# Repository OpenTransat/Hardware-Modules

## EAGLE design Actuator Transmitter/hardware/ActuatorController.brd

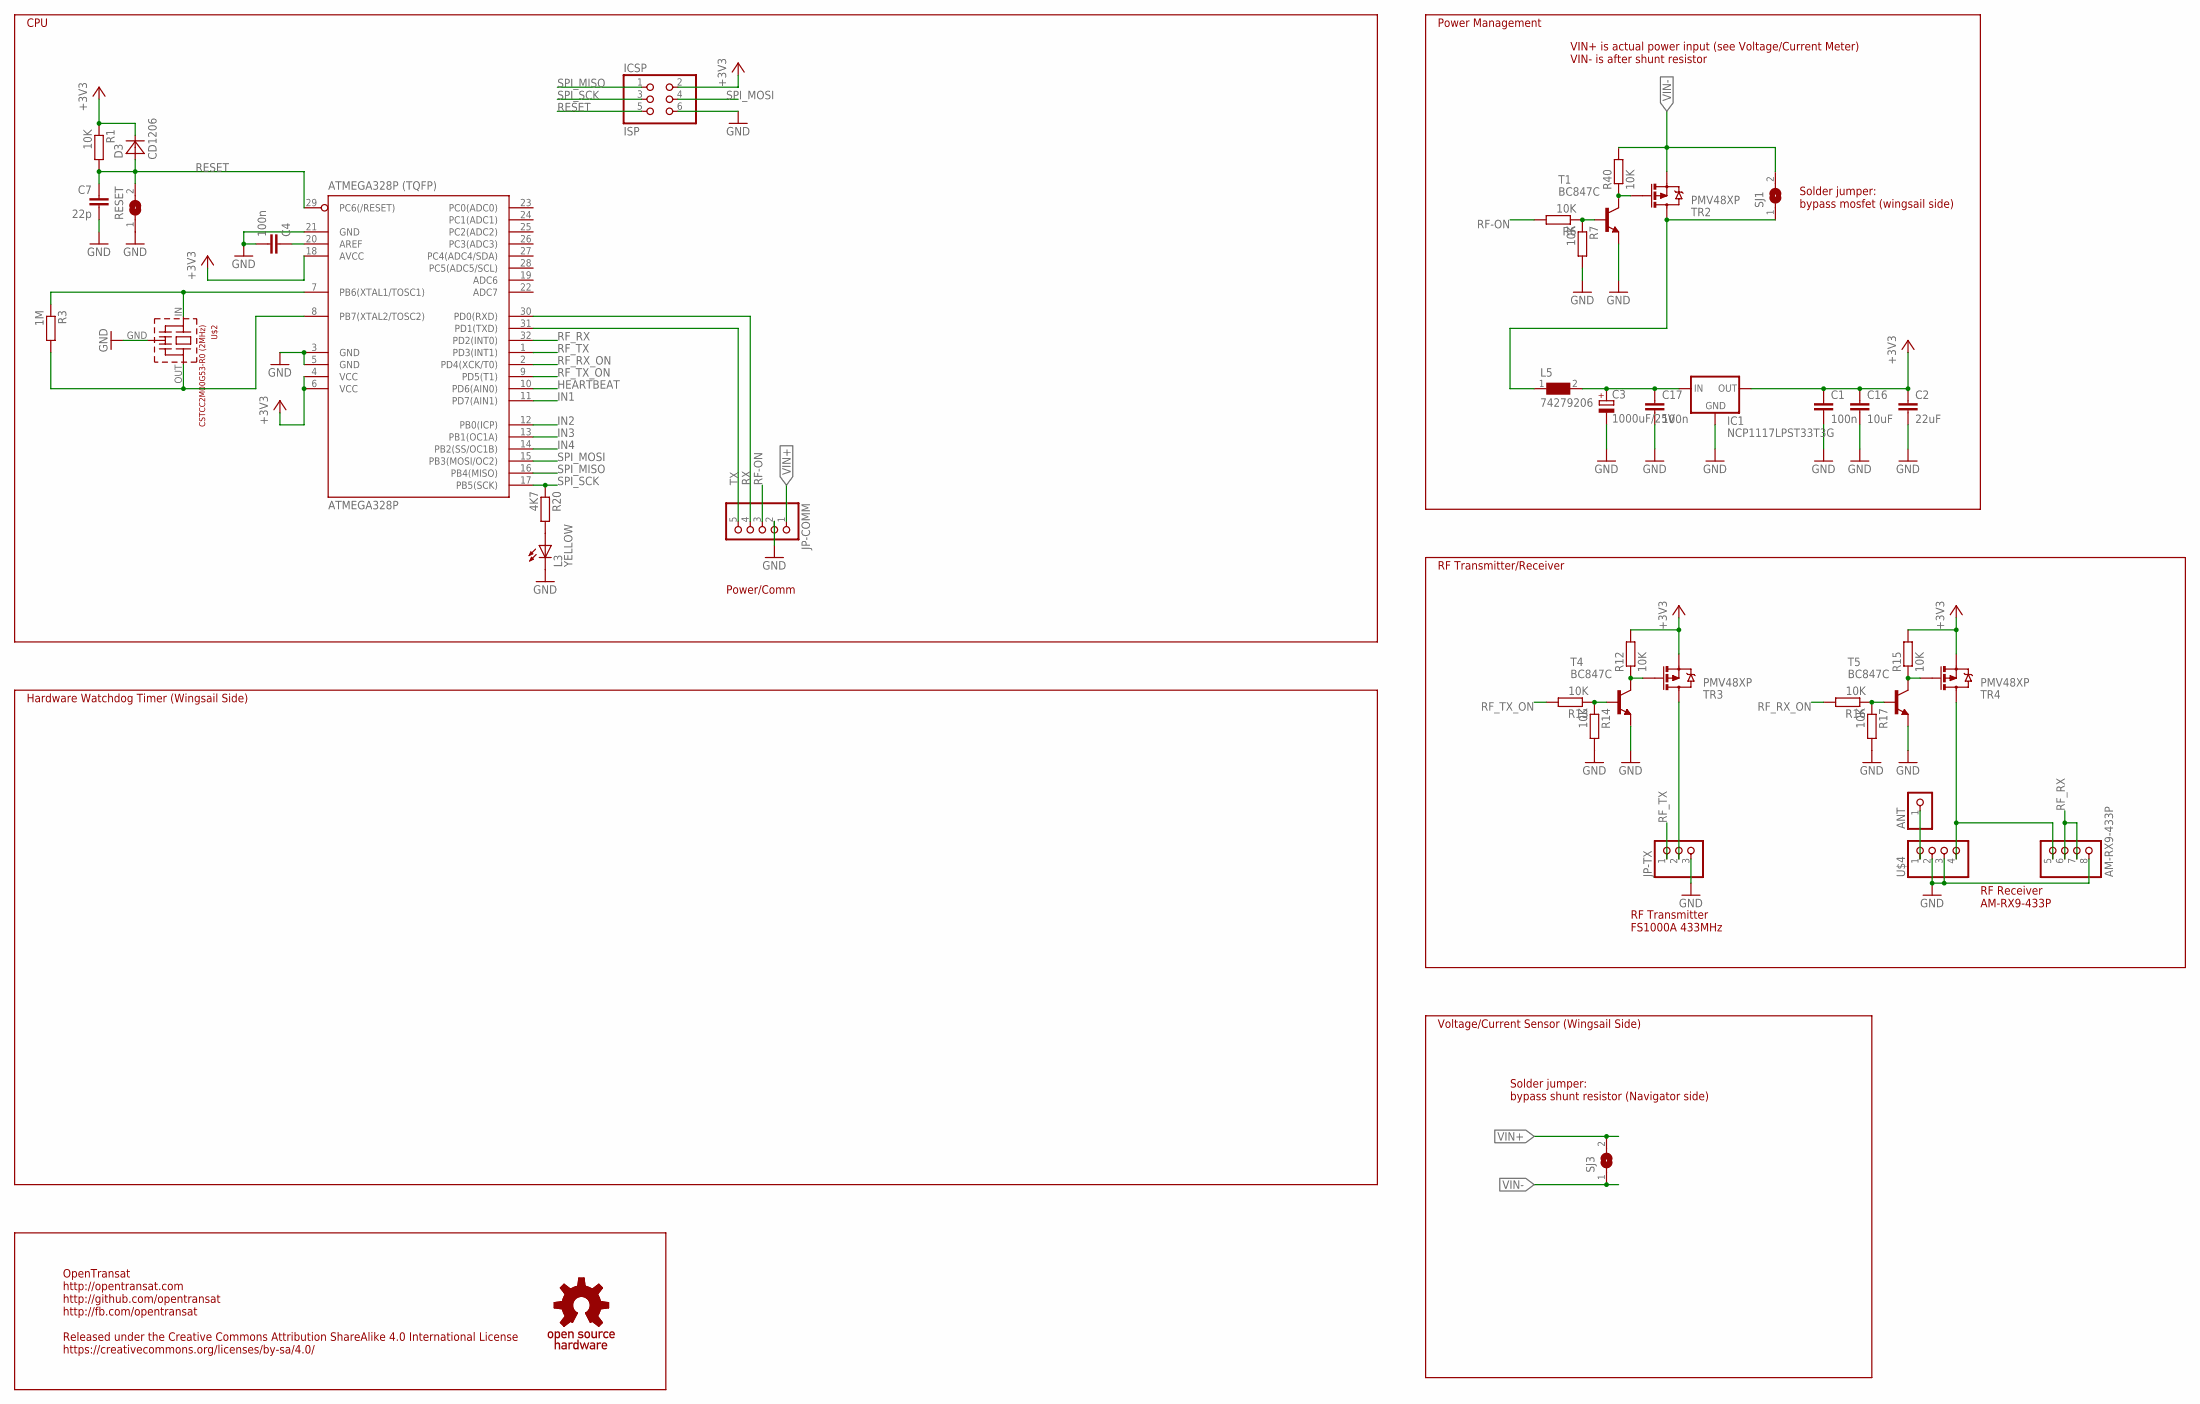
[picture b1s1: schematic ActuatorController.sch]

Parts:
ANT: PINHD-1X1; 1X01
ATMEGA328P: ATMEGA328P (TQFP); TQFP32-08
C1, C4, C17: 100n; C0603
C2: 22uF; C1210
C3: 1000uF/25V; E5-10,5
C7: 22p; C0603
C16: 10uF; C1206
D3: CD1206; R1206
IC1: NCP1117LPST33T3G; SOT223
ICSP: ISP; 2X03
JP-COMM: PINHD-1X5/90; 1X05/90
JP-TX: PINHD-1X3; 1X03
L3: YELLOW; CHIPLED_0805
L5: 74279206; 0805
R1, R6, R7, R12, R13, R14, R15, R16, R17, R40: 10K; R0603
R3: 1M; R0603
R20: 4K7; R0603
RESET: SJW
SJ1, SJ3: SJ
T1, T4, T5: BC847C; SOT23
TR2, TR3, TR4: PMV48XP; SOT23-3
U$1: OSHW_S; OSHWS
U$2: CSTCC2M00G53-R0 (2MHz); CSTCC
U$4: AM-RX9-433P; 1X04

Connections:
+3V3: ATMEGA328P.4 (VCC), ATMEGA328P.6 (VCC), ATMEGA328P.18 (AVCC), C1.1, C2.1, C16.1, D3.2 (C), IC1.2 (OUT), IC1.4 (OUT), ICSP.2, R1.1, R12.2, R15.2, TR3.2 (S), TR4.2 (S)
AREF: ATMEGA328P.20 (AREF), C4.1
GND: ATMEGA328P.3 (GND), ATMEGA328P.5 (GND), ATMEGA328P.21 (GND), C1.2, C2.2, C3.-, C4.2, C7.2, C16.2, C17.2, IC1.1 (GND), ICSP.6, JP-COMM.2, JP-TX.3, L3.C, R7.2, R14.2, R17.2, RESET.1, T1.2 (E), T4.2 (E), T5.2 (E), U$2.GND, U$4.2, U$4.3, U$4.8
HEARTBEAT: ATMEGA328P.10 (PD6(AIN0))
IN1: ATMEGA328P.11 (PD7(AIN1))
IN2: ATMEGA328P.12 (PB0(ICP))
IN3: ATMEGA328P.13 (PB1(OC1A))
IN4: ATMEGA328P.14 (PB2(SS/OC1B))
unnamed: C3.+, C17.1, IC1.3 (IN), L5.2
unnamed: L3.A, R20.2
unnamed: R6.1, R7.1, T1.1 (B)
unnamed: R12.1, T4.3 (C), TR3.1 (G)
unnamed: R13.1, R14.1, T4.1 (B)
unnamed: ANT.1, U$4.1
unnamed: JP-TX.2, TR3.3 (D)
unnamed: R15.1, T5.3 (C), TR4.1 (G)
unnamed: R16.1, R17.1, T5.1 (B)
unnamed: TR4.3 (D), U$4.4, U$4.5
unnamed: R40.1, T1.3 (C), TR2.1 (G)
RESET: ATMEGA328P.29 (PC6(/RESET)), C7.1, D3.1 (A), ICSP.5, R1.2, RESET.2
RF-ON: JP-COMM.3, R6.2
RF_RX: ATMEGA328P.32 (PD2(INT0)), U$4.6, U$4.7
RF_RX_ON: ATMEGA328P.2 (PD4(XCK/T0)), R16.2
RF_TX: ATMEGA328P.1 (PD3(INT1)), JP-TX.1
RF_TX_ON: ATMEGA328P.9 (PD5(T1)), R13.2
RX: ATMEGA328P.30 (PD0(RXD)), JP-COMM.4
SPI_MISO: ATMEGA328P.16 (PB4(MISO)), ICSP.1
SPI_MOSI: ATMEGA328P.15 (PB3(MOSI/OC2)), ICSP.4
SPI_SCK: ATMEGA328P.17 (PB5(SCK)), ICSP.3, R20.1
TX: ATMEGA328P.31 (PD1(TXD)), JP-COMM.5
VBAT-ON: L5.1, SJ1.1, TR2.3 (D)
VIN+: JP-COMM.1, SJ3.2
VIN-: R40.2, SJ1.2, SJ3.1, TR2.2 (S)
XTAL1: ATMEGA328P.8 (PB7(XTAL2/TOSC2)), R3.2, U$2.OUT
XTAL2: ATMEGA328P.7 (PB6(XTAL1/TOSC1)), R3.1, U$2.IN

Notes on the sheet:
OpenTransat http://opentransat.com http://github.com/opentransat http://fb.com/opentransat Released under the Creative Commons Attribution ShareAlike 4.0 International License https://creativecommons.org/licenses/by-sa/4.0/
Power Management
CPU
Voltage/Current Sensor (Wingsail Side)
VIN+ is actual power input (see Voltage/Current Meter) VIN- is after shunt resistor
Power/Comm
RF Receiver AM-RX9-433P
RF Transmitter FS1000A 433MHz
RF Transmitter/Receiver
Hardware Watchdog Timer (Wingsail Side)
Solder jumper: bypass mosfet (wingsail side)
Solder jumper: bypass shunt resistor (Navigator side)

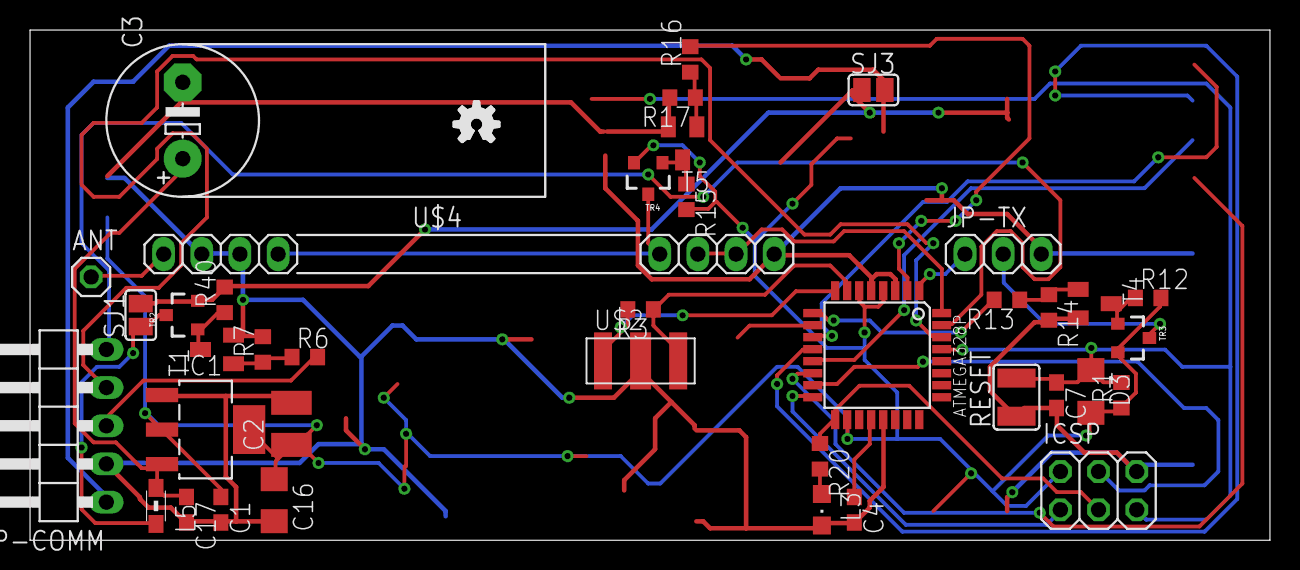
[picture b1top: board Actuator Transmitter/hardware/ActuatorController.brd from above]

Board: 2 copper layers, 82.5 x 34.0 mm, 40 parts (0 on the bottom side), 30 nets.

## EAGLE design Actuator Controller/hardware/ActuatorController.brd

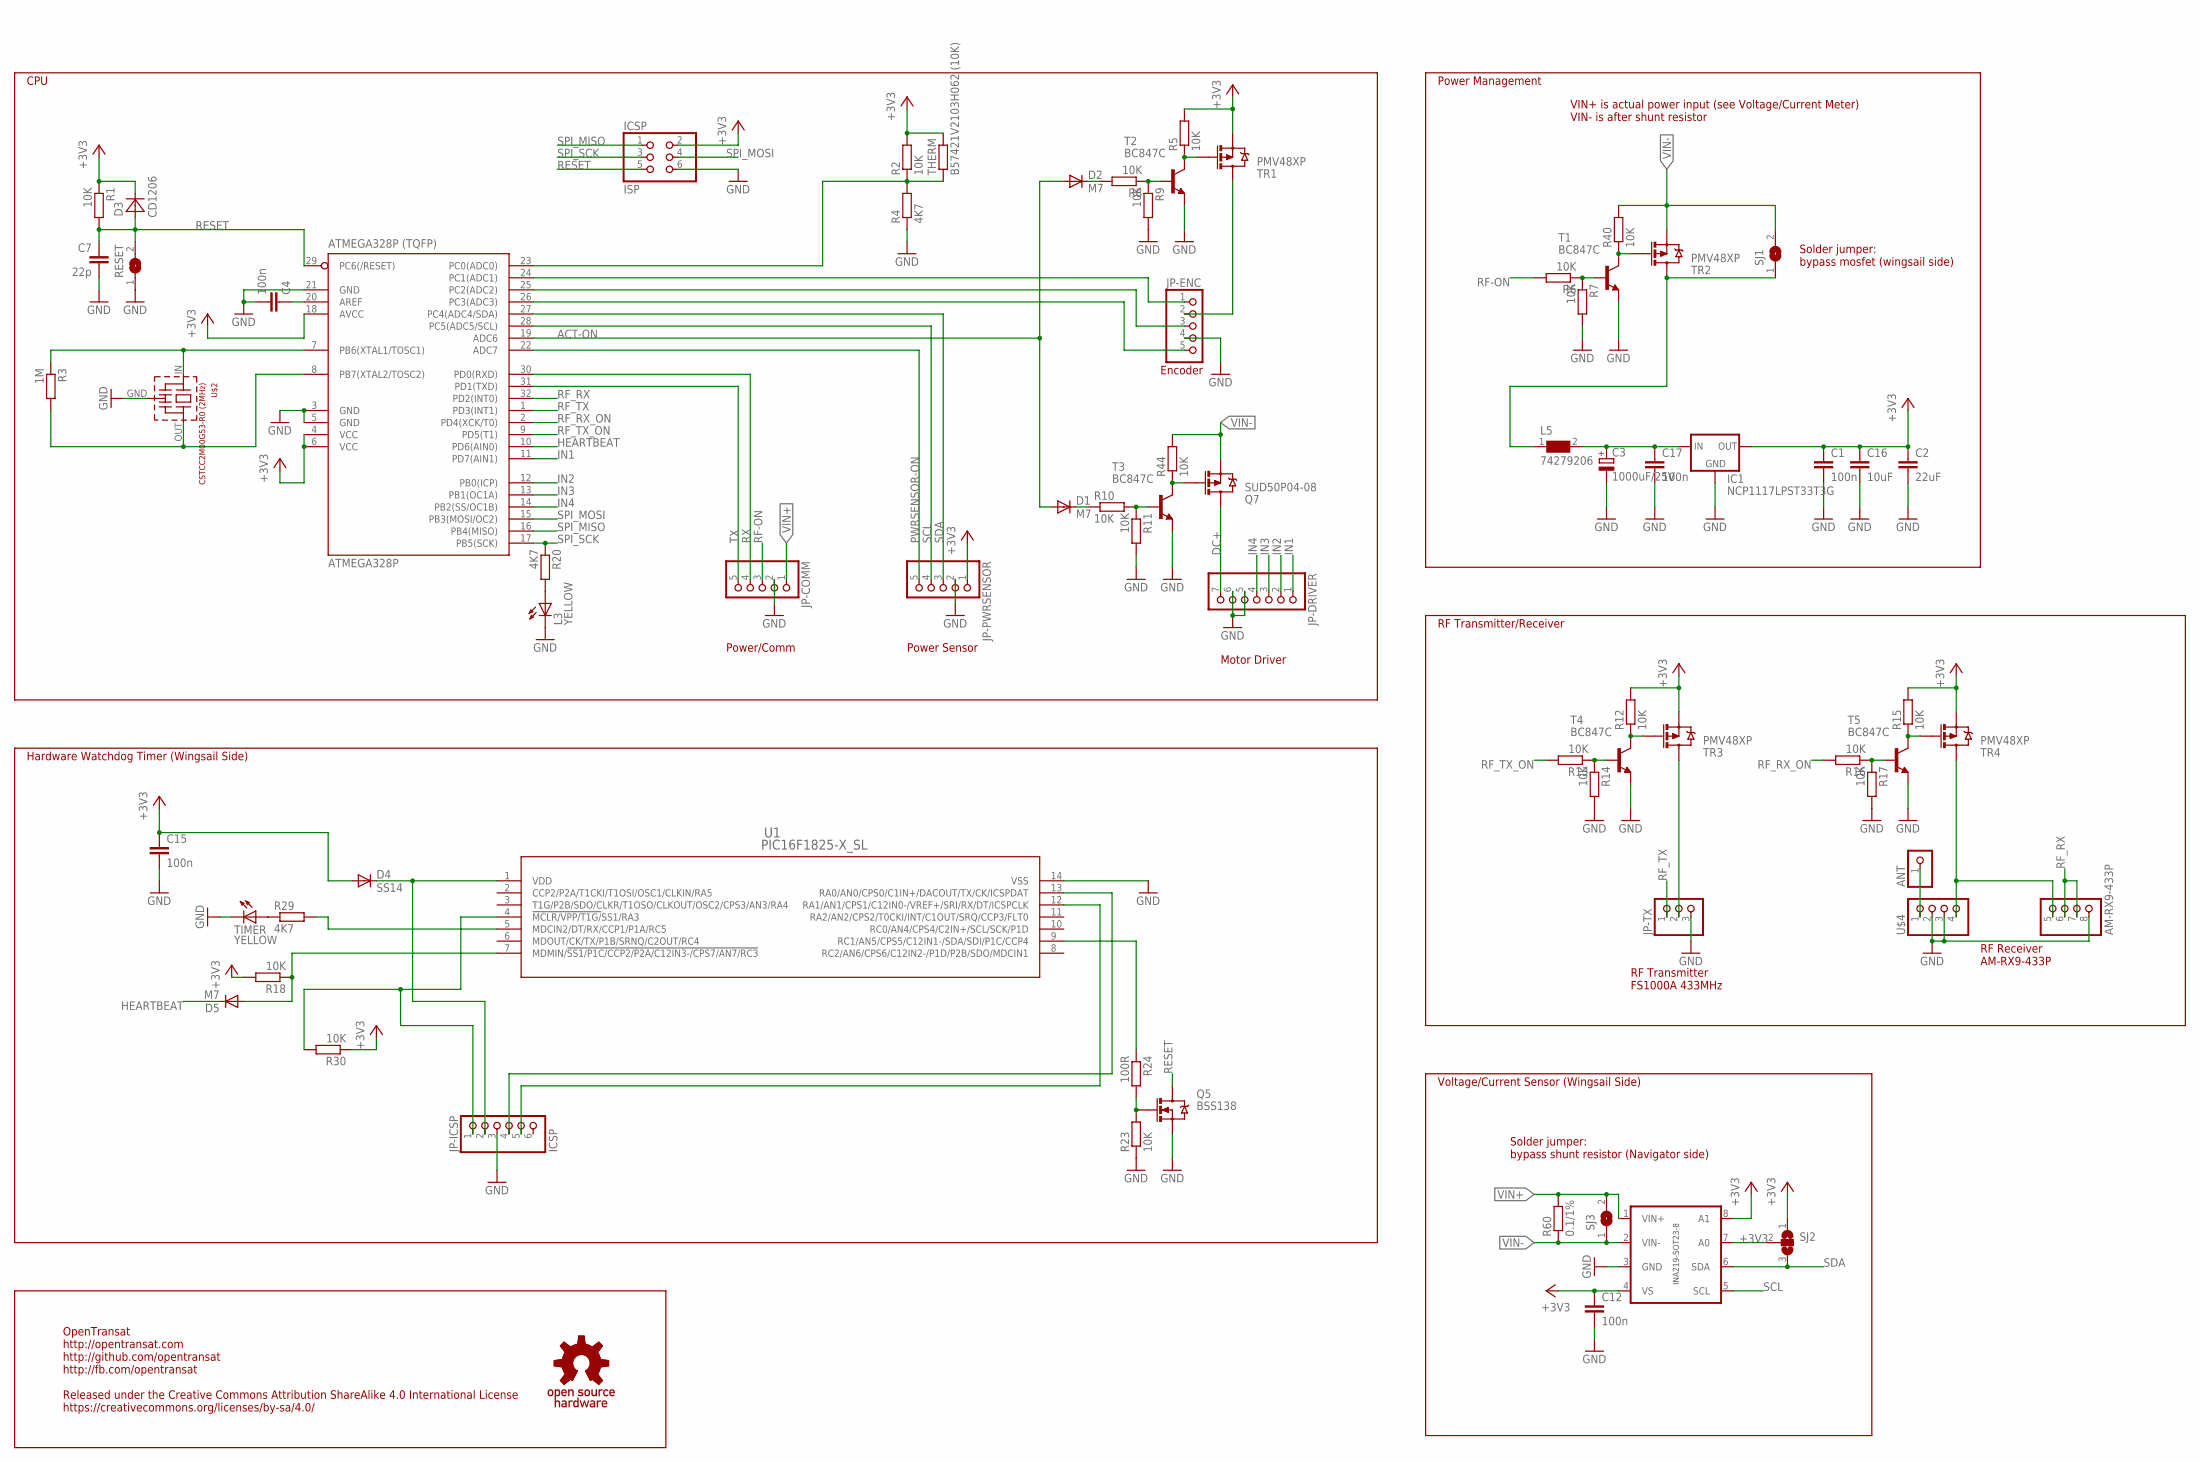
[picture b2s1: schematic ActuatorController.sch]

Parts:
ANT: PINHD-1X1; 1X01
ATMEGA328P: ATMEGA328P (TQFP); TQFP32-08
C1, C4, C12, C15, C17: 100n; C0603
C2: 22uF; C1210
C3: 1000uF/25V; E5-10,5
C7: 22p; C0603
C16: 10uF; C1206
D1, D2, D5: M7; DO-214AC
D3: CD1206; R1206
D4: SS14; DO214AC
IC1: NCP1117LPST33T3G; SOT223
ICSP: ISP; 2X03
JP-COMM: PINHD-1X5/90; 1X05/90
JP-DRIVER: PINHD-1X7/90; 1X07/90
JP-ENC: PINHD-1X5/90; 1X05/90
JP-ICSP: ICSP; 1X06
JP-PWRSENSOR: PINHD-1X5/90; 1X05/90
JP-TX: PINHD-1X3; 1X03
L3: YELLOW; CHIPLED_0805
L5: 74279206; 0805
Q5: BSS138; SOT23-3
Q7: SUD50P04-08; D-PAK_TO252AA
R1, R2, R5, R6, R7, R8, R9, R10, R11, R12, R13, R14, R15, R16, R17, R18, R23, R30, R40, R44: 10K; R0603
R3: 1M; R0603
R4, R20, R29: 4K7; R0603
R24: 100R; R0603
R60: 0.1/1%; R2512
RESET: SJW
SJ1, SJ3: SJ
SJ2: SJ2W; SJ_2
T1, T2, T3, T4, T5: BC847C; SOT23
THERM: B57421V2103H062 (10K); R0603
TIMER: YELLOW; CHIPLED_0805
TR1, TR2, TR3, TR4: PMV48XP; SOT23-3
U1: PIC16F1825-X_SL; SOIC14-N_MC
U$1: OSHW_S; OSHWS
U$2: CSTCC2M00G53-R0 (2MHz); CSTCC
U$3: INA219-SOT23-8; SOT23-8
U$4: AM-RX9-433P; 1X04

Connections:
+3V3: ATMEGA328P.4 (VCC), ATMEGA328P.6 (VCC), ATMEGA328P.18 (AVCC), C1.1, C2.1, C12.1, C15.1, C16.1, D3.2 (C), D4.A, IC1.2 (OUT), IC1.4 (OUT), ICSP.2, JP-PWRSENSOR.1, R1.1, R2.2, R5.2, R12.2, R15.2, R18.2, R30.1, SJ2.1, SJ2.2, THERM.2, TR1.2 (S), TR3.2 (S), TR4.2 (S), U$3.4 (VS), U$3.7 (A0), U$3.8 (A1)
ACT-ON: ATMEGA328P.19 (ADC6), D1.A, D2.A
AREF: ATMEGA328P.20 (AREF), C4.1
DC+: JP-DRIVER.7, Q7.2 (D)
GND: ATMEGA328P.3 (GND), ATMEGA328P.5 (GND), ATMEGA328P.21 (GND), C1.2, C2.2, C3.-, C4.2, C7.2, C12.2, C15.2, C16.2, C17.2, IC1.1 (GND), ICSP.6, JP-COMM.2, JP-DRIVER.5, JP-DRIVER.6, JP-ENC.4, JP-ICSP.3, JP-PWRSENSOR.2, JP-TX.3, L3.C, Q5.2 (S), R4.1, R7.2, R9.2, R11.2, R14.2, R17.2, R23.1, RESET.1, T1.2 (E), T2.2 (E), T3.2 (E), T4.2 (E), T5.2 (E), TIMER.C, U1.14 (VSS), U$2.GND, U$3.3 (GND), U$4.2, U$4.3, U$4.8
HEARTBEAT: ATMEGA328P.10 (PD6(AIN0)), D5.C
IN1: ATMEGA328P.11 (PD7(AIN1)), JP-DRIVER.1
IN2: ATMEGA328P.12 (PB0(ICP)), JP-DRIVER.2
IN3: ATMEGA328P.13 (PB1(OC1A)), JP-DRIVER.3
IN4: ATMEGA328P.14 (PB2(SS/OC1B)), JP-DRIVER.4
unnamed: C3.+, C17.1, IC1.3 (IN), L5.2
unnamed: R5.1, T2.3 (C), TR1.1 (G)
unnamed: L3.A, R20.2
unnamed: R10.2, R11.1, T3.1 (B)
unnamed: ATMEGA328P.23 (PC0(ADC0)), R2.1, R4.2, THERM.1
unnamed: ATMEGA328P.24 (PC1(ADC1)), JP-ENC.1
unnamed: ATMEGA328P.25 (PC2(ADC2)), JP-ENC.3
unnamed: ATMEGA328P.26 (PC3(ADC3)), JP-ENC.5
unnamed: R8.1, R9.1, T2.1 (B)
unnamed: R6.1, R7.1, T1.1 (B)
unnamed: JP-ENC.2, TR1.3 (D)
unnamed: D2.C, R8.2
unnamed: D1.C, R10.1
unnamed: R12.1, T4.3 (C), TR3.1 (G)
unnamed: R13.1, R14.1, T4.1 (B)
unnamed: ANT.1, U$4.1
unnamed: JP-TX.2, TR3.3 (D)
unnamed: R15.1, T5.3 (C), TR4.1 (G)
unnamed: R16.1, R17.1, T5.1 (B)
unnamed: TR4.3 (D), U$4.4, U$4.5
unnamed: D5.A, R18.1, U1.7 (MDMIN/!SS1/P1C/CCP2/P2A/C12IN3-/CPS7/AN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)
unnamed: JP-ICSP.4, U1.13 (RA0/AN0/CPS0/C1IN+/DACOUT/TX/CK/ICSPDAT)
unnamed: Q7.1 (G), R44.1, T3.3 (C)
unnamed: R40.1, T1.3 (C), TR2.1 (G)
unnamed: JP-ICSP.1, R30.2, U1.4 (!MCLR/VPP/T1G/!SS1/RA3)
unnamed: JP-ICSP.5, U1.12 (RA1/AN1/CPS1/C12IN0-/VREF+/SRI/RX/DT/IC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)
unnamed: D4.C, JP-ICSP.2, U1.1 (VDD)
unnamed: R24.1, U1.9 (RC1/AN5/CPS5/C12IN1-/SDA/SDI/P1C/CCP4)
unnamed: Q5.1 (G), R23.2, R24.2
unnamed: R29.2, U1.5 (MDCIN2/DT/RX/CCP1/P1A/RC5)
unnamed: R29.1, TIMER.A
PWRSENSOR-ON: ATMEGA328P.22 (ADC7), JP-PWRSENSOR.5
RESET: ATMEGA328P.29 (PC6(/RESET)), C7.1, D3.1 (A), ICSP.5, Q5.3 (D), R1.2, RESET.2
RF-ON: JP-COMM.3, R6.2
RF_RX: ATMEGA328P.32 (PD2(INT0)), U$4.6, U$4.7
RF_RX_ON: ATMEGA328P.2 (PD4(XCK/T0)), R16.2
RF_TX: ATMEGA328P.1 (PD3(INT1)), JP-TX.1
RF_TX_ON: ATMEGA328P.9 (PD5(T1)), R13.2
RX: ATMEGA328P.30 (PD0(RXD)), JP-COMM.4
SCL: ATMEGA328P.28 (PC5(ADC5/SCL)), JP-PWRSENSOR.4, U$3.5 (SCL)
SDA: ATMEGA328P.27 (PC4(ADC4/SDA)), JP-PWRSENSOR.3, SJ2.3, U$3.6 (SDA)
SPI_MISO: ATMEGA328P.16 (PB4(MISO)), ICSP.1
SPI_MOSI: ATMEGA328P.15 (PB3(MOSI/OC2)), ICSP.4
SPI_SCK: ATMEGA328P.17 (PB5(SCK)), ICSP.3, R20.1
TX: ATMEGA328P.31 (PD1(TXD)), JP-COMM.5
VBAT-ON: L5.1, SJ1.1, TR2.3 (D)
VIN+: JP-COMM.1, R60.2, SJ3.2, U$3.1 (VIN+)
VIN-: Q7.3 (S), R40.2, R44.2, R60.1, SJ1.2, SJ3.1, TR2.2 (S), U$3.2 (VIN-)
XTAL1: ATMEGA328P.8 (PB7(XTAL2/TOSC2)), R3.2, U$2.OUT
XTAL2: ATMEGA328P.7 (PB6(XTAL1/TOSC1)), R3.1, U$2.IN

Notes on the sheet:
OpenTransat http://opentransat.com http://github.com/opentransat http://fb.com/opentransat Released under the Creative Commons Attribution ShareAlike 4.0 International License https://creativecommons.org/licenses/by-sa/4.0/
Power Management
CPU
Voltage/Current Sensor (Wingsail Side)
VIN+ is actual power input (see Voltage/Current Meter) VIN- is after shunt resistor
Motor Driver
Power Sensor
Power/Comm
Encoder
RF Receiver AM-RX9-433P
RF Transmitter FS1000A 433MHz
RF Transmitter/Receiver
Hardware Watchdog Timer (Wingsail Side)
Solder jumper: bypass mosfet (wingsail side)
Solder jumper: bypass shunt resistor (Navigator side)

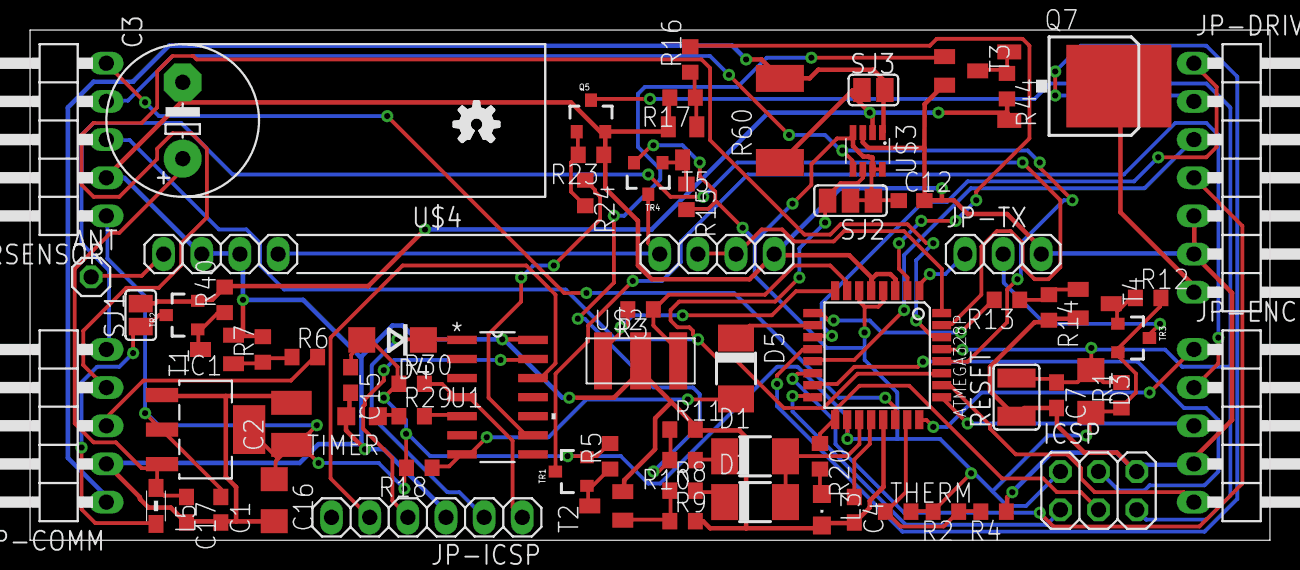
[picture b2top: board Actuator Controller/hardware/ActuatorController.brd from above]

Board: 2 copper layers, 82.5 x 34.0 mm, 74 parts (0 on the bottom side), 60 nets.

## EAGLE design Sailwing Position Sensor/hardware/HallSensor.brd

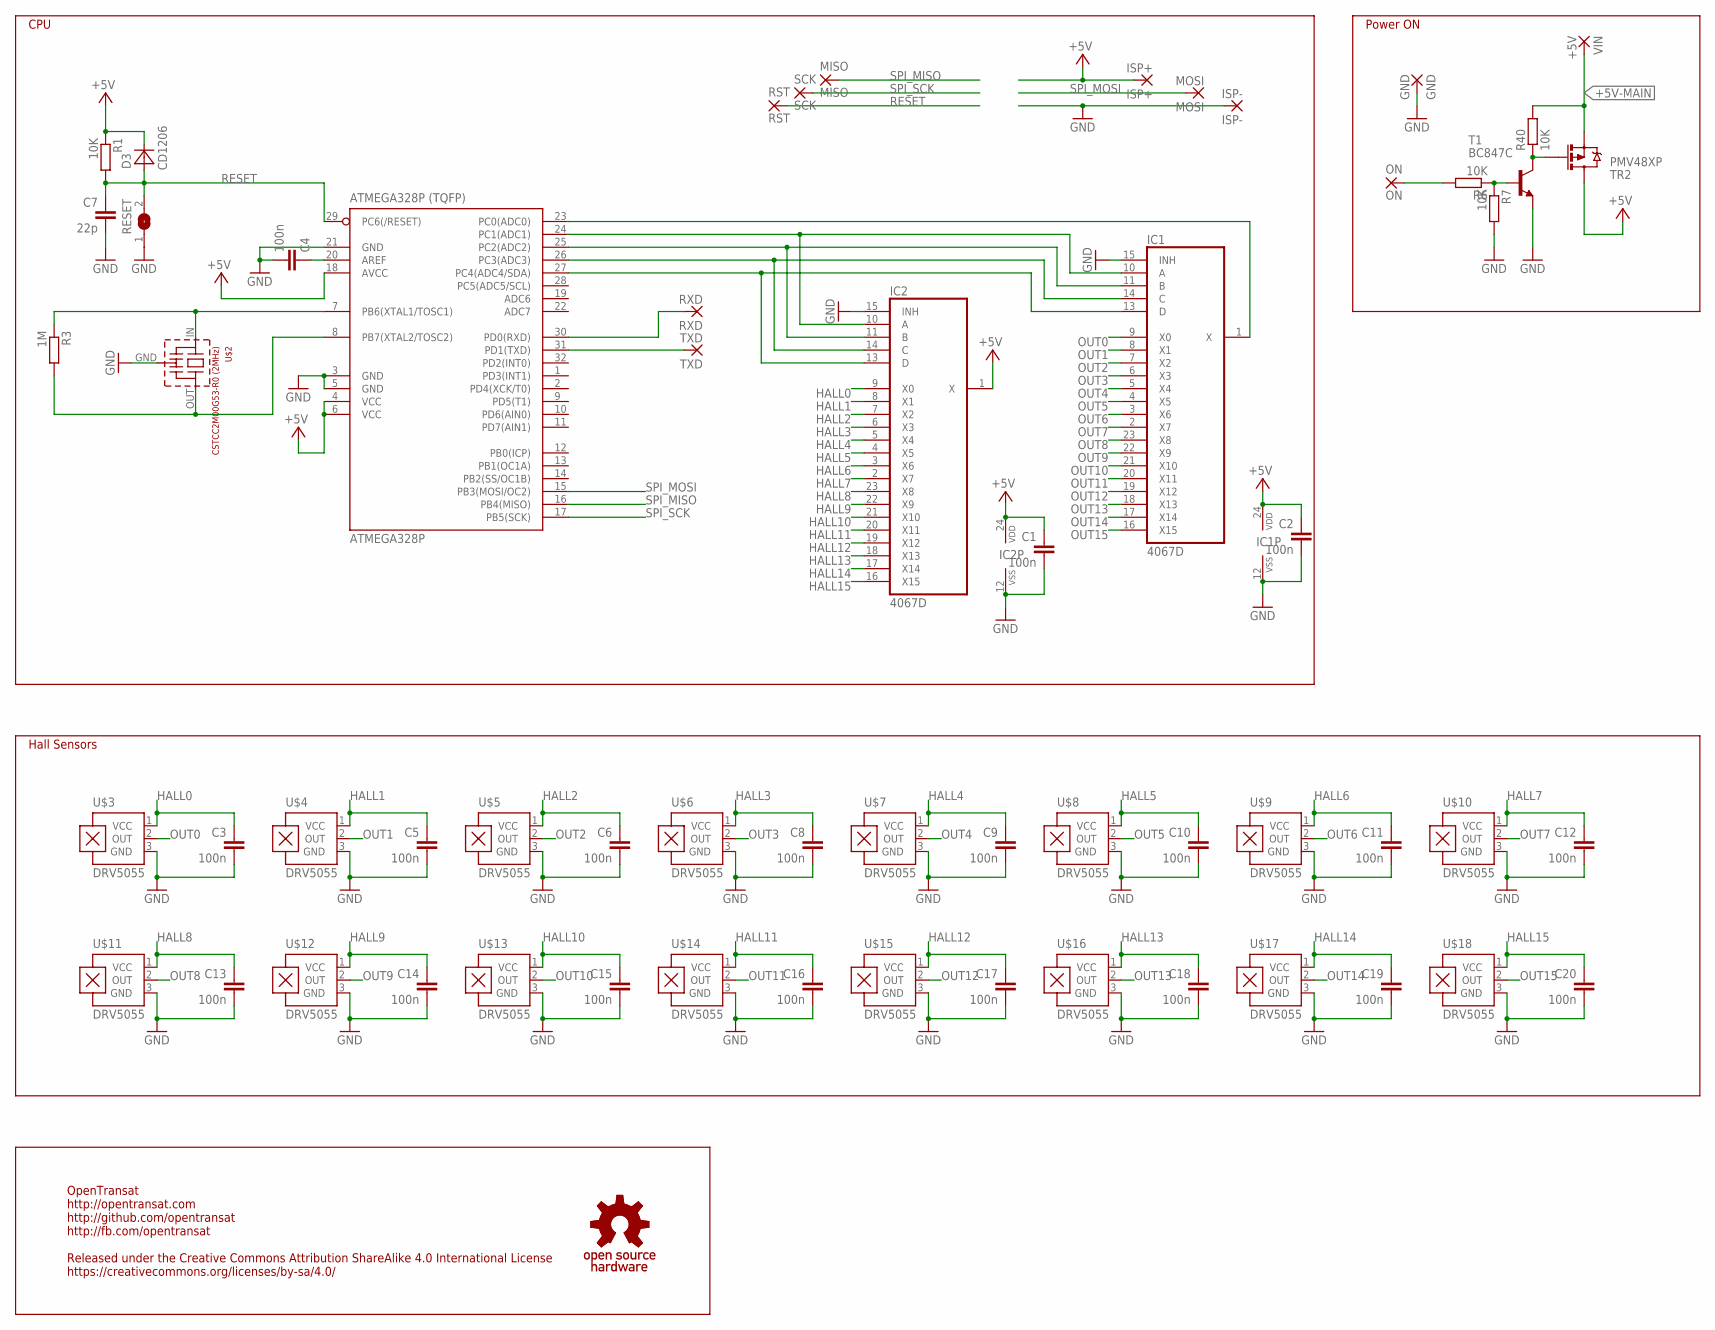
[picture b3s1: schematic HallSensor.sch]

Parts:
ATMEGA328P: ATMEGA328P (TQFP); TQFP32-08
C1, C2, C3, C4, C5, C6, C8, C9, C10, C11, C12, C13, C14, C15, C16, C17, C18, C19, C20: 100n; C0603
C7: 22p; C0603
D3: CD1206; R1206
GND: GND; SMD2,54-5,08
IC1, IC2: 4067D; SO24W
ISP+: ISP+; SMD2,54-5,08
ISP-: ISP-; SMD2,54-5,08
MISO: MISO; SMD2,54-5,08
MOSI: MOSI; SMD2,54-5,08
ON: ON; SMD2,54-5,08
R1, R6, R7, R40: 10K; R0603
R3: 1M; R0603
RESET: SJW
RST: RST; SMD2,54-5,08
RXD: RXD; SMD2,54-5,08
SCK: SCK; SMD2,54-5,08
T1: BC847C; SOT23
TR2: PMV48XP; SOT23-3
TXD: TXD; SMD2,54-5,08
U$1: OSHW_S; OSHWS
U$2: CSTCC2M00G53-R0 (2MHz); CSTCC
U$3, U$4, U$5, U$6, U$7, U$8, U$9, U$10, U$11, U$12, U$13, U$14, U$15, U$16, U$17, U$18: DRV5055; SOT23
VIN: +5V; SMD2,54-5,08

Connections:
+5V: ATMEGA328P.4 (VCC), ATMEGA328P.6 (VCC), ATMEGA328P.18 (AVCC), C1.1, C2.1, D3.2 (C), IC1.24 (VDD), IC2.1 (X), IC2.24 (VDD), ISP+.1, R1.1, TR2.3 (D)
+5V-MAIN: R40.2, TR2.2 (S), VIN.1
AREF: ATMEGA328P.20 (AREF), C4.1
GND: ATMEGA328P.3 (GND), ATMEGA328P.5 (GND), ATMEGA328P.21 (GND), C1.2, C2.2, C3.2, C4.2, C5.2, C6.2, C7.2, C8.2, C9.2, C10.2, C11.2, C12.2, C13.2, C14.2, C15.2, C16.2, C17.2, C18.2, C19.2, C20.2, GND.1, IC1.12 (VSS), IC1.15 (INH), IC2.12 (VSS), IC2.15 (INH), ISP-.1, R7.2, RESET.1, T1.2 (E), U$2.GND, U$3.3 (GND), U$4.3 (GND), U$5.3 (GND), U$6.3 (GND), U$7.3 (GND), U$8.3 (GND), U$9.3 (GND), U$10.3 (GND), U$11.3 (GND), U$12.3 (GND), U$13.3 (GND), U$14.3 (GND), U$15.3 (GND), U$16.3 (GND), U$17.3 (GND), U$18.3 (GND)
HALL0: C3.1, IC2.9 (X0), U$3.1 (VCC)
HALL1: C5.1, IC2.8 (X1), U$4.1 (VCC)
HALL2: C6.1, IC2.7 (X2), U$5.1 (VCC)
HALL3: C8.1, IC2.6 (X3), U$6.1 (VCC)
HALL4: C9.1, IC2.5 (X4), U$7.1 (VCC)
HALL5: C10.1, IC2.4 (X5), U$8.1 (VCC)
HALL6: C11.1, IC2.3 (X6), U$9.1 (VCC)
HALL7: C12.1, IC2.2 (X7), U$10.1 (VCC)
HALL8: C13.1, IC2.23 (X8), U$11.1 (VCC)
HALL9: C14.1, IC2.22 (X9), U$12.1 (VCC)
HALL10: C15.1, IC2.21 (X10), U$13.1 (VCC)
HALL11: C16.1, IC2.20 (X11), U$14.1 (VCC)
HALL12: C17.1, IC2.19 (X12), U$15.1 (VCC)
HALL13: C18.1, IC2.18 (X13), U$16.1 (VCC)
HALL14: C19.1, IC2.17 (X14), U$17.1 (VCC)
HALL15: C20.1, IC2.16 (X15), U$18.1 (VCC)
L13: ATMEGA328P.23 (PC0(ADC0)), IC1.1 (X)
unnamed: R6.1, R7.1, T1.1 (B)
unnamed: ATMEGA328P.30 (PD0(RXD)), RXD.1
unnamed: ATMEGA328P.31 (PD1(TXD)), TXD.1
unnamed: ON.1, R6.2
unnamed: ATMEGA328P.24 (PC1(ADC1)), IC1.10 (A), IC2.10 (A)
unnamed: ATMEGA328P.25 (PC2(ADC2)), IC1.11 (B), IC2.11 (B)
unnamed: ATMEGA328P.26 (PC3(ADC3)), IC1.14 (C), IC2.14 (C)
unnamed: ATMEGA328P.27 (PC4(ADC4/SDA)), IC1.13 (D), IC2.13 (D)
unnamed: R40.1, T1.3 (C), TR2.1 (G)
OUT0: IC1.9 (X0), U$3.2 (OUT)
OUT1: IC1.8 (X1), U$4.2 (OUT)
OUT2: IC1.7 (X2), U$5.2 (OUT)
OUT3: IC1.6 (X3), U$6.2 (OUT)
OUT4: IC1.5 (X4), U$7.2 (OUT)
OUT5: IC1.4 (X5), U$8.2 (OUT)
OUT6: IC1.3 (X6), U$9.2 (OUT)
OUT7: IC1.2 (X7), U$10.2 (OUT)
OUT8: IC1.23 (X8), U$11.2 (OUT)
OUT9: IC1.22 (X9), U$12.2 (OUT)
OUT10: IC1.21 (X10), U$13.2 (OUT)
OUT11: IC1.20 (X11), U$14.2 (OUT)
OUT12: IC1.19 (X12), U$15.2 (OUT)
OUT13: IC1.18 (X13), U$16.2 (OUT)
OUT14: IC1.17 (X14), U$17.2 (OUT)
OUT15: IC1.16 (X15), U$18.2 (OUT)
RESET: ATMEGA328P.29 (PC6(/RESET)), C7.1, D3.1 (A), R1.2, RESET.2, RST.1
SPI_MISO: ATMEGA328P.16 (PB4(MISO)), MISO.1
SPI_MOSI: ATMEGA328P.15 (PB3(MOSI/OC2)), MOSI.1
SPI_SCK: ATMEGA328P.17 (PB5(SCK)), SCK.1
XTAL1: ATMEGA328P.8 (PB7(XTAL2/TOSC2)), R3.2, U$2.OUT
XTAL2: ATMEGA328P.7 (PB6(XTAL1/TOSC1)), R3.1, U$2.IN

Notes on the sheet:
OpenTransat http://opentransat.com http://github.com/opentransat http://fb.com/opentransat Released under the Creative Commons Attribution ShareAlike 4.0 International License https://creativecommons.org/licenses/by-sa/4.0/
CPU
Power ON
Hall Sensors

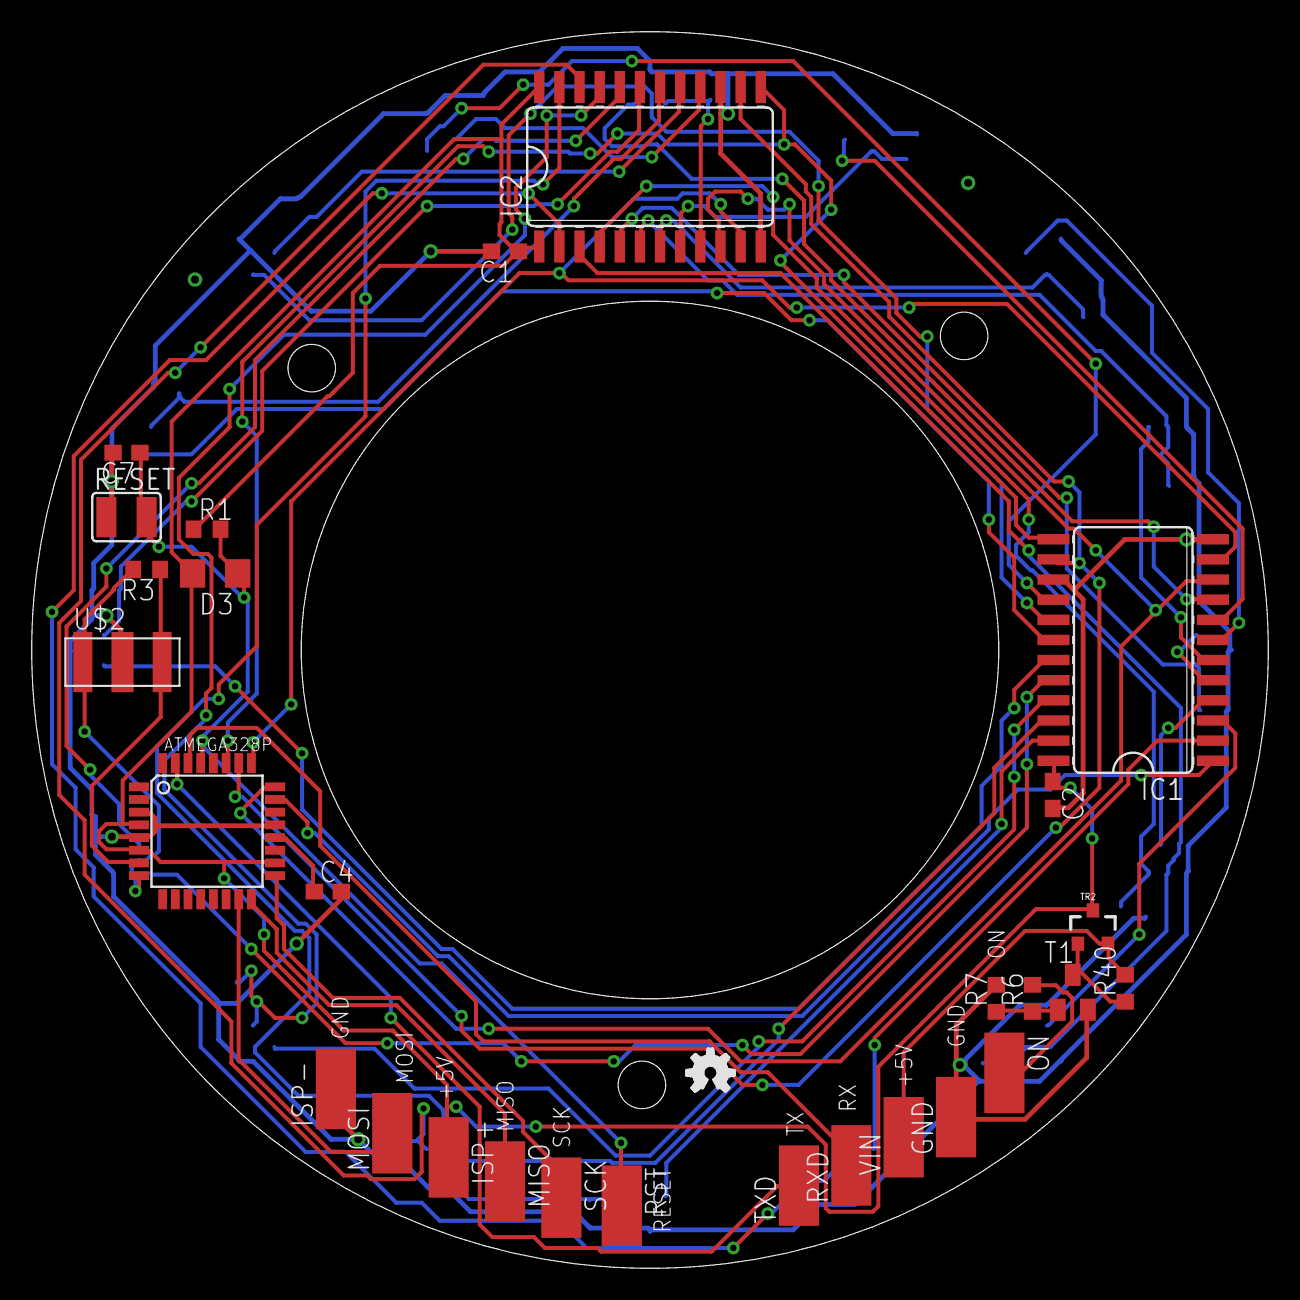
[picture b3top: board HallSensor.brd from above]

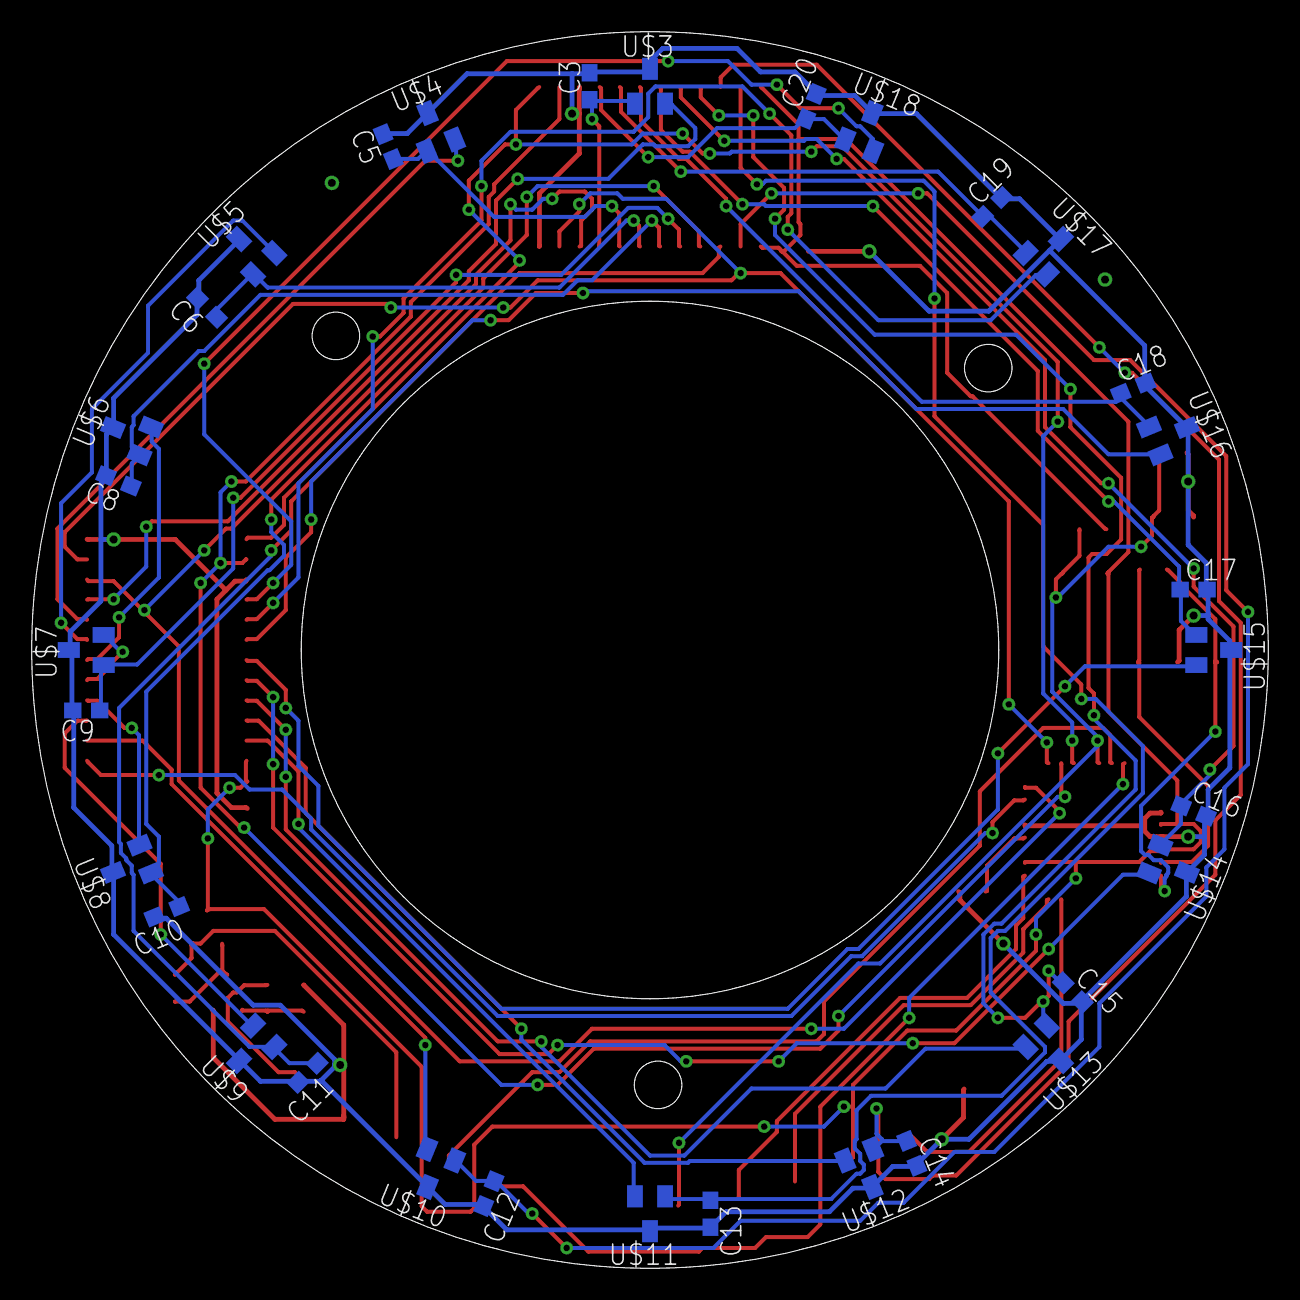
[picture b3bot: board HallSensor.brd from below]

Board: 2 copper layers, 78.0 x 78.0 mm, 61 parts (32 on the bottom side), 52 nets.

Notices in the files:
compass/software/arduino/pins_arduino.h:
Copyright (c) 2007 David A. Mellis
Public License along with this library; if not, write to the
Free Software Foundation, Inc., 59 Temple Place, Suite 330,
Boston, MA  02111-1307  USA
parts and their libraries:
Wurth_Elektronik_Passive_rev15b: Copyright: Würth Elektronik
SparkFun-Aesthetics: Licensing: Creative Commons ShareAlike 4.0 International - https://creativecommons.org/licenses/by-sa/4.0
